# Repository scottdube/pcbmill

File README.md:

# pcbmill

Cockpit for milling PCBs on the Tormach 1100MX. Wraps the proven pipeline —
`pcb2gcode → post.py / postdrill.py → applymap.py` plus the smartprobe
grid-probing program — behind one job directory, one **Regenerate all**
button, a 10-point verification suite, and a printable run sheet.

It runs the existing tools (vendored unchanged in `pcbmill/vendor/`); it does
not reimplement CAM and never talks to the machine.

## Install

```bash
cd pcbmill
python3 -m venv .venv
.venv/bin/pip install -e .
```

External requirements (Homebrew): `pcb2gcode` (3.0.4) and `gerbv`
(used to rasterise the Gerber for sliver prediction).

## Web UI

```bash
.venv/bin/pcbmill serve --jobs-root ~/PCBMill
```

Then open http://127.0.0.1:8337. Left rail = pipeline stages with status
badges; the verification report is the landing page for a job. The command
is run from the repo root (`.venv` is relative).

**PCBMill.app** does both from Finder/Dock/Spotlight: `app/build.sh` builds it
into `~/Applications`. It starts the server only if nothing answers on 8337,
then opens the browser. The server is detached and keeps running after the app
exits; log in `~/Library/Logs/pcbmill.log`, stop with `pkill -f 'pcbmill serve'`.
The repo path is baked in at build time, so rebuild if the repo moves.

## CLI (every UI action, scriptable)

```bash
pcbmill new jobdir --back B_Cu.gbr --drill merged.drl --pcb board.kicad_pcb
cd jobdir
pcbmill status                 # inputs, artifact staleness, readiness
pcbmill drill-info             # parsed drill table (before anything generates)
pcbmill consolidate            # drill->bit mapping + annulus check
pcbmill set cam.isolation_width 0.030
pcbmill frame 4.3372 3.2478 --verify   # fixed frame from the KiCad-page
                               # transform (FR5.3): x-offset=-MX, y-offset=MY;
                               # --verify proves drill byte-stability
pcbmill solve-offsets          # measurement-based placement solver
pcbmill probe-gen              # emit smartprobe program (frozen motion + config)
pcbmill probe-import probe-results.ngc   # QA: span, plane, roughness
pcbmill touchoff               # highest-node touch-off + validation nodes
pcbmill regen                  # the WHOLE chain, then verify
pcbmill verify                 # 10-check suite; blocks "job ready" on FAIL
pcbmill runsheet               # printable operator sheet
```

## Job model

A job is one self-contained directory:

```
job/
  job.json      manifest: params, input hashes, artifact fingerprints
  inputs/       copies of the KiCad exports
  probe/        generated probe program + imported probe-results.ngc
  out/          generated G-code - NEVER edited by hand (edits are detected)
```

Any parameter or input change flips downstream artifacts **stale**
(fingerprint mismatch); hand edits in `out/` show as **TAMPERED**. Both
block "job ready" until you Regenerate all.

## The verification suite (why this exists)

0. Inputs — back Gerber present; ONE merged MixedPlating Excellon (split
   PTH/NPTH pairs rejected)
1. Extents — every file vs blank and probe map
2. Mirror proof — drill X histogram must match the Excellon reversed;
   spans equal to 4 decimals; top column group lands on the mirrored side
3. Hole count — G-code plunges == Excellon holes
4. Tool block audit — T-numbers in the assigned set (≥600 so M6 never
   fires the ATC), G43 H match, G54, G30, no bare feed-before-tool
5. Z audit — cutting Z == map ± zwork; rapids == zsafe + map mean; drill
   breakthrough ≥ 3 thou into backer but above the damage limit; retracts
   clear copper; probe #7 clears copper
6. Clamp count — 0 for cutting ops (map must cover the toolpath)
7. Comment/paren lint — PathPilot-safe: balanced, no nesting, O-words paired
8. Staleness — all hashes current
9. Sliver prediction — gerbv render + distance transform; gap regions the
   isolation band won't consume = floating copper. FAIL within 1 mm of a
   solderable pad, PLANNED inside declared pour-exclusion rule areas,
   WARN elsewhere. Suggests the minimum isolation-width that zeroes FAILs.
10. Design intake lint (report-only) — zone clearance, solid pours, round
    pads on fine-pitch rows, pour-exclusion areas
12. Fixed frame (FR5.3) — zero-start is forbidden (the bounding-box origin
    silently shifts every output when isolation-width changes); explicit
    offsets required; full verify regenerates at a second isolation-width
    and proves the drill G-code is byte-identical

## Machine conventions baked in (configurable per job)

- G54 Z0 on the **backer**; the map carries absolute copper height;
  applymap runs in absolute mode (relative mode requires an explicit
  confirmation — its failure mode is a 70-thou crash)
- Isolation cutter touch-off is **electrical**, mandatory (ETS reads
  +4.1 thou high vs the work frame), and its program applies H600 with
  **no G37**; every other tool (drills, outline cutter) is measured by
  G37/ETS in-program
- Probe is T99/H99; spindle max 10k RPM; manual-prompt tools ≥ T600
- The pcb2gcode autoleveller is never emitted (`al-*` produces Mach3 G31)
- The coordinate frame is always `zero-start=0` with explicit offsets from
  the KiCad-page transform (`x-offset = −MX`, `y-offset = MY`, optionally a
  DRO-read placement delta); on this mirrored back-side board x-offset acts
  in mirrored X — frames are verified by measurement, never assumption

## Tests

```bash
.venv/bin/python -m pytest tests/
```

19 tests: byte-level recreation of board 1 (sln-geo-aux-heat) from its
real inputs, plus one test per historical bug (front=, split drills,
positive x-offset on the mirrored frame, stale/tampered outputs, probe #7
below copper, short probe grid, ATC tool numbers, single-pass slivers on
the ESP32 rows).

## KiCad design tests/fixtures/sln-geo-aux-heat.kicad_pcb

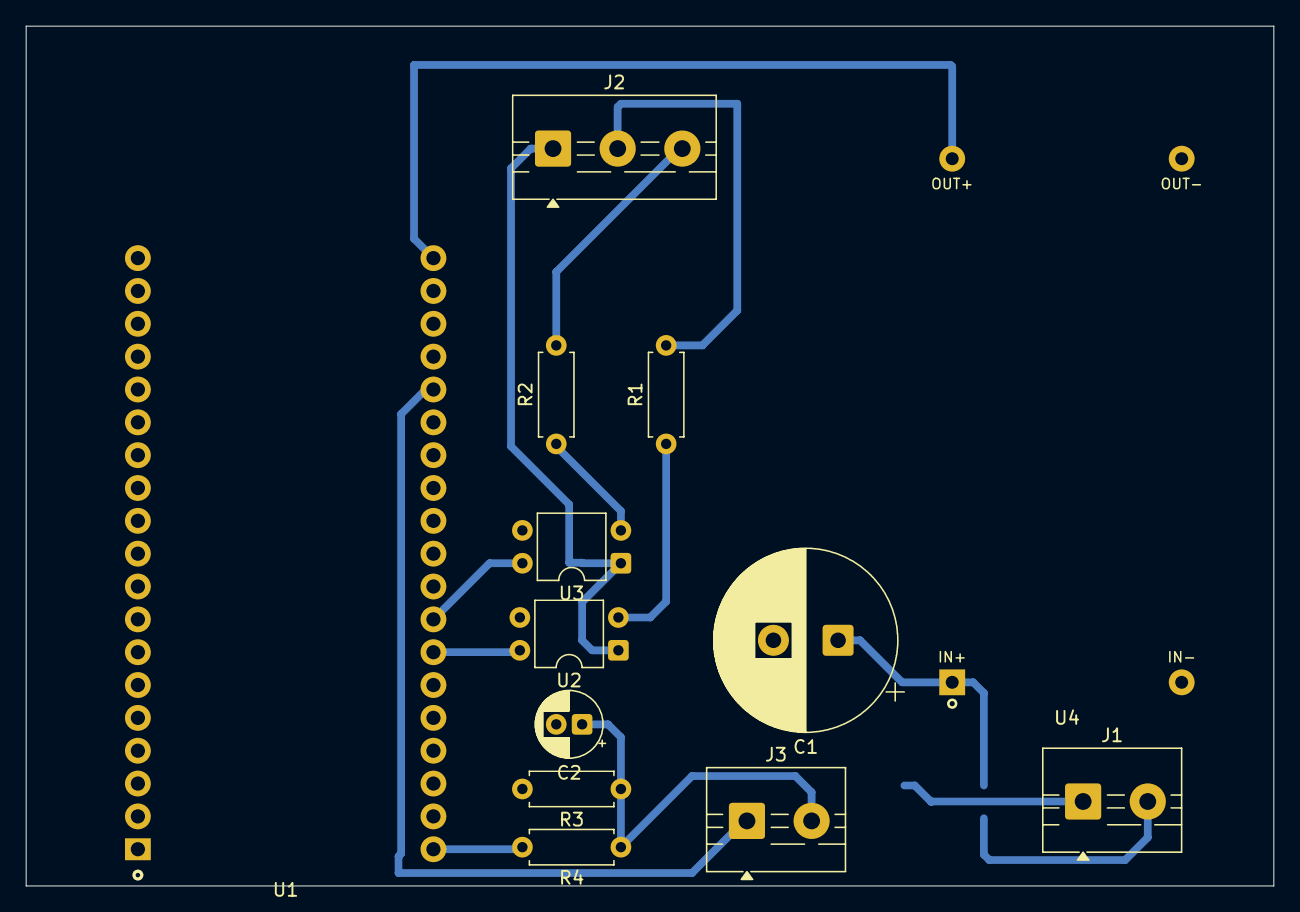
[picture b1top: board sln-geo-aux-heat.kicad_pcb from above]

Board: 2 copper layers, 96.5 x 66.5 mm, 14 parts (1 on the bottom side), 15 nets.

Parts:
C1: 470µF/63V; CP_Radial_D14.0mm_P5.00mm
C2: 10µf; CP_Radial_D5.0mm_P2.00mm
D1: MB10S; TO-269AA
J1: 24VAC R+C; TerminalBlock_MaiXu_MX126-5.0-02P_1x02_P5.00mm
J2: Screw_Terminal_01x03; TerminalBlock_MaiXu_MX126-5.0-03P_1x03_P5.00mm
J3: CT; TerminalBlock_MaiXu_MX126-5.0-02P_1x02_P5.00mm
R1, R2: 3.3k; R_Axial_DIN0207_L6.3mm_D2.5mm_P7.62mm_Horizontal
R3, R4: 100k; R_Axial_DIN0207_L6.3mm_D2.5mm_P7.62mm_Horizontal
U1: NodeMCU-32S; NodeMCU-32S_38pin_THT
U2, U3: PC817; DIP-4_W7.62mm
U4: LM2596-40V; LM2596_Module_THT

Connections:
+3V3: R4.2, U1.20 (3V3)
+5V: U1.38 (5V), U4.3 (OUT+)
/AC_C: D1.2, J1.2
/AC_H: D1.4, J1.1
/BIAS: C2.1, J3.2, R3.1, R4.1
/BLK_24VDC: J2.1, U2.1, U3.1
/CMD_W1_N: U1.26 (P32), U2.4
/CMD_W2_N: U1.27 (P33), U3.4
/CT_ADC: J3.1, U1.34 (P13)
/EH1_WHT: J2.2, R1.2
/EH2_RED: J2.3, R2.2
/VBUS_38V: C1.1, D1.1 (+), U4.1 (IN+)
GND: C1.2, C2.2, D1.3 (-), R3.2, U1.1 (GND), U1.37 (GND), U2.3, U3.3, U4.2 (IN-), U4.4 (OUT-)
unnamed: R1.1, U2.2
unnamed: R2.1, U3.2
